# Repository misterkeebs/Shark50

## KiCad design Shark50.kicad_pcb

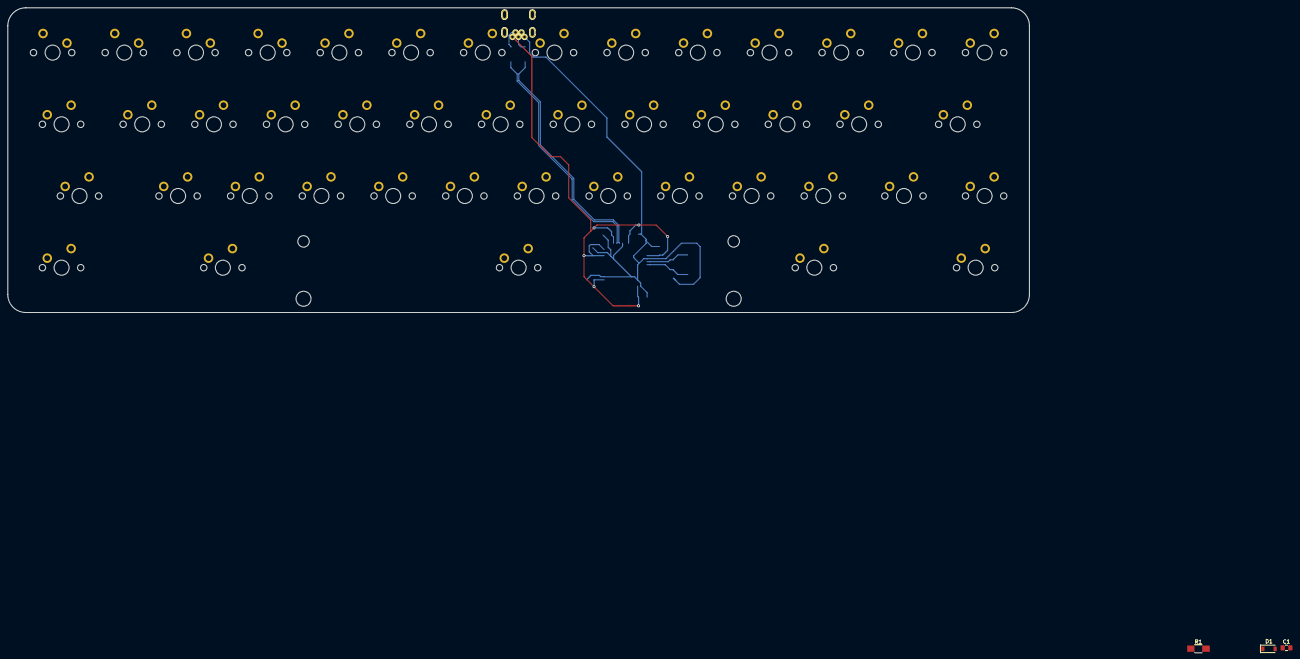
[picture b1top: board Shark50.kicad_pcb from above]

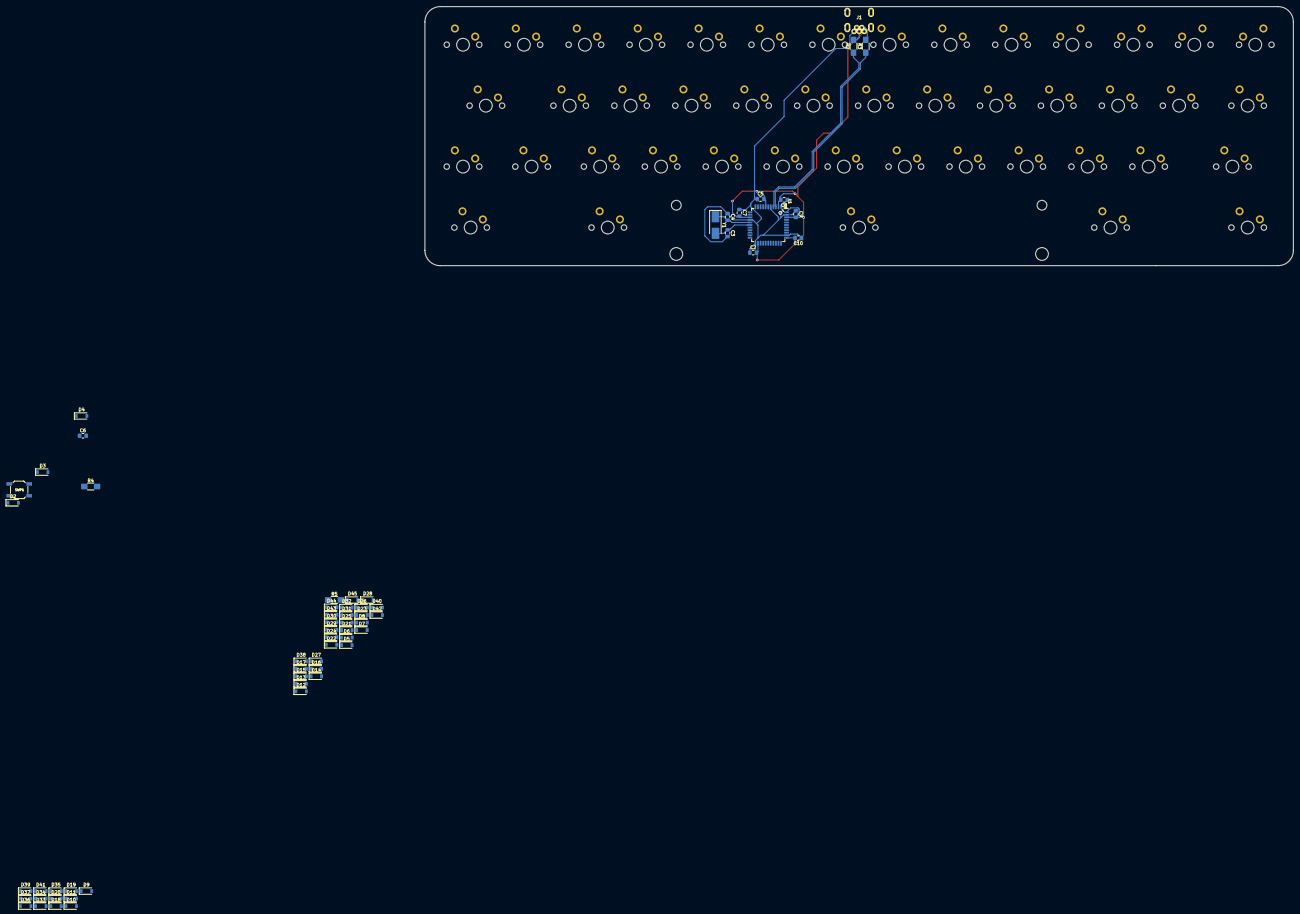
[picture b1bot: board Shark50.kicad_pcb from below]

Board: 2 copper layers, 271.5 x 81.0 mm, 109 parts (102 on the bottom side), 74 nets.

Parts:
C1, C3, C4: 22pF; C_0805_2012Metric_Pad1.15x1.40mm_HandSolder
C2: 10uF; C_0805_2012Metric_Pad1.15x1.40mm_HandSolder
C5, C9: 1u; C_0805_2012Metric_Pad1.15x1.40mm_HandSolder
C6: 1uF; C_0805_2012Metric_Pad1.15x1.40mm_HandSolder
C7, C8, C10: 100n; C_0805_2012Metric_Pad1.15x1.40mm_HandSolder
D1, D2, D3, D4, D5, D6, D7, D8, D9, D10, D11, D12, D13, D14, D15, D16, D17, D18, D19, D20, D21, D22, D23, D24, D25, D26, D27, D28, D29, D30, D31, D32, D33, D34, D35, D36, D37, D38, D39, D40, D41, D42, D43, D44, D45: 1N4148W; D_SOD-123
J1: USB_B_Mini; USB_MiniB_XM7D-0512
R1: 10k; R_1206_HandSoldering
R2, R3: 22; R_1206_HandSoldering
R4: 1k; R_1206_HandSoldering
R5: 330; R_1206_HandSoldering
SW1: Esc; MX100
SW2: Q; MX100
SW3: W; MX100
SW4: E; MX100
SW5: R; MX100
SW6: T; MX100
SW7: Y; MX100
SW8: U; MX100
SW9: I; MX100
SW10: O; MX100
SW11: P; MX100
SW12: [; MX100
SW13: ]; MX100
SW14: BkSpc; MX100
SW15: Tab_125; MX125
SW16: LShift_175; MX175
SW17: LCtrl_125; MX125
SW18: A; MX100
SW19: Z; MX100
SW20: S; MX100
SW21: X; MX100
SW22: LAlt_125; MX125
SW23: D; MX100
SW24: C; MX100
SW25: F; MX100
SW26: V; MX100
SW27: G; MX100
SW28: B; MX100
SW29: Space_7; MX700
SW30: H; MX100
SW31: N; MX100
SW32: J; MX100
SW33: M; MX100
SW34: K; MX100
SW35: <; MX100
SW36: L; MX100
SW37: >; MX100
SW38: ;; MX100
SW39: /; MX100
SW40: RAlt_125; MX125
SW41: '; MX100
SW42: RShift_125; MX125
SW43: Enter_175; MX175
SW44: Fn; MX100
SW45: RCtr_125; MX125
SWP1: SW_Push; smdPushBtn
U1: ATmega32U4-AU; TQPF-44_10x10mm_P0.8mm
Y1: 16MHz; Crystal_SMD_5032-2pin_5.0x3.2mm_HandSoldering

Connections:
+5V: C2.2, C5.2, C7.2, C8.2, C9.2, C10.2, J1.1, R1.2, U1.2, U1.7, U1.14, U1.24, U1.34, U1.42, U1.44
/DN: R3.1, U1.3
/DP: R2.1, U1.4
Col1: SW1.1, SW15.1, SW16.1, SW17.1
Col2: SW2.1, SW18.1, SW19.1
Col3: SW3.1, SW20.1, SW21.1, SW22.1
Col4: SW4.1, SW23.1, SW24.1
Col5: SW5.1, SW25.1, SW26.1
Col6: SW6.1, SW27.1, SW28.1, SW29.1
Col7: SW7.1, SW30.1, SW31.1
Col8: SW8.1, SW32.1, SW33.1
Col9: SW9.1, SW34.1, SW35.1
Col10: SW10.1, SW36.1, SW37.1
Col11: SW11.1, SW38.1, SW39.1, SW40.1
Col12: SW12.1, SW41.1, SW42.1
Col13: SW13.1, SW43.1, SW44.1, SW45.1
GND: C2.1, C3.2, C4.1, C5.1, C6.2, C7.1, C8.1, C9.1, C10.1, J1.5, R4.1, R5.1, U1.5, U1.15, U1.23, U1.35, U1.43
unnamed: C1.1, SWP1.1
unnamed: C3.1, U1.17
unnamed: C4.2, U1.16
unnamed: C6.1, U1.6
unnamed: D1.2, SW1.2
unnamed: D2.2, SW2.2
unnamed: D3.2, SW3.2
unnamed: D4.2, SW4.2
unnamed: D5.2, SW5.2
unnamed: D6.2, SW6.2
unnamed: D7.2, SW7.2
unnamed: D8.2, SW8.2
unnamed: D9.2, SW9.2
unnamed: D10.2, SW10.2
unnamed: D11.2, SW11.2
unnamed: D12.2, SW12.2
unnamed: D13.2, SW13.2
unnamed: D14.2, SW14.2
unnamed: D15.2, SW15.2
unnamed: D16.2, SW16.2
unnamed: D17.1, D22.1, D29.1, D40.1, D45.1
unnamed: D17.2, SW17.2
unnamed: D18.2, SW18.2
unnamed: D19.2, SW19.2
unnamed: D20.2, SW20.2
unnamed: D21.2, SW21.2
unnamed: D22.2, SW22.2
unnamed: D23.2, SW23.2
unnamed: D24.2, SW24.2
unnamed: D25.2, SW25.2
unnamed: D26.2, SW26.2
unnamed: D27.2, SW27.2
unnamed: D28.2, SW28.2
unnamed: D29.2, SW29.2
unnamed: D30.2, SW30.2
unnamed: D31.2, SW31.2
unnamed: D32.2, SW32.2
unnamed: D33.2, SW33.2
unnamed: D34.2, SW34.2
unnamed: D35.2, SW35.2
unnamed: D36.2, SW36.2
unnamed: D37.2, SW37.2
unnamed: D38.2, SW38.2
unnamed: D39.2, SW39.2
unnamed: D40.2, SW40.2
unnamed: D41.2, SW41.2
unnamed: D42.2, SW42.2
unnamed: D43.2, SW43.2
unnamed: D44.2, SW44.2
unnamed: D45.2, SW45.2
unnamed: J1.2, R3.2
unnamed: J1.3, R2.2
unnamed: R4.2, U1.33
RST: C1.2, SWP1.2, U1.13
Row1: D1.1, D2.1, D3.1, D4.1, D5.1, D6.1, D7.1, D8.1, D9.1, D10.1, D11.1, D12.1, D13.1, D14.1
Row2: D15.1, D18.1, D20.1, D23.1, D25.1, D27.1, D30.1, D32.1, D34.1, D36.1, D38.1, D41.1, D43.1
Row3: D16.1, D19.1, D21.1, D24.1, D26.1, D28.1, D31.1, D33.1, D35.1, D37.1, D39.1, D42.1, D44.1

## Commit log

2019-09-06 chore: initial commit
2019-09-12 feat: added KLE JSON file
2019-09-12 chore: removed schematic bak file
2019-09-12 feat: added matrix first row
2019-09-12 feat: matrix ready
2019-09-12 feat: matrix symbols
2019-09-12 feat: added switches layout to the PCB
2019-09-13 feat: added USB connector to the PCB
2019-10-10 Finished multi layout wiring
2020-11-21 feat: beginning of MCU routing
